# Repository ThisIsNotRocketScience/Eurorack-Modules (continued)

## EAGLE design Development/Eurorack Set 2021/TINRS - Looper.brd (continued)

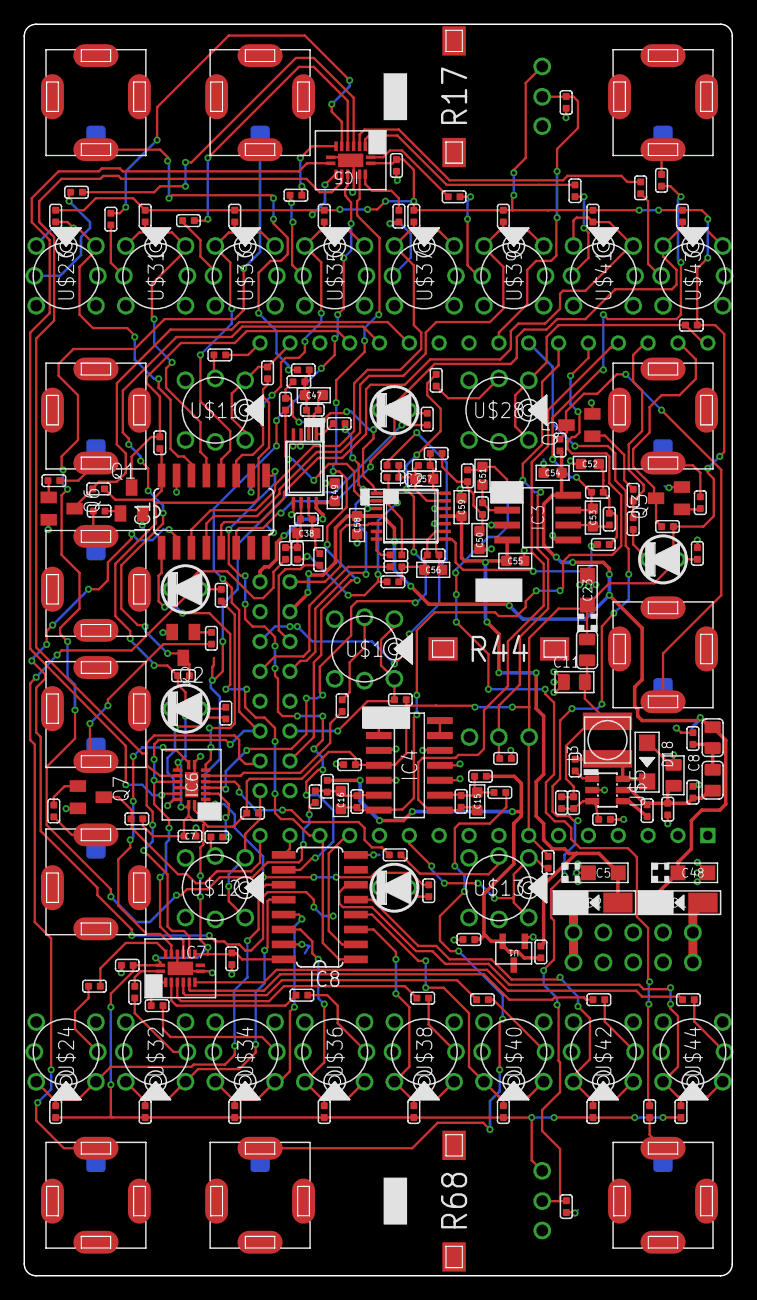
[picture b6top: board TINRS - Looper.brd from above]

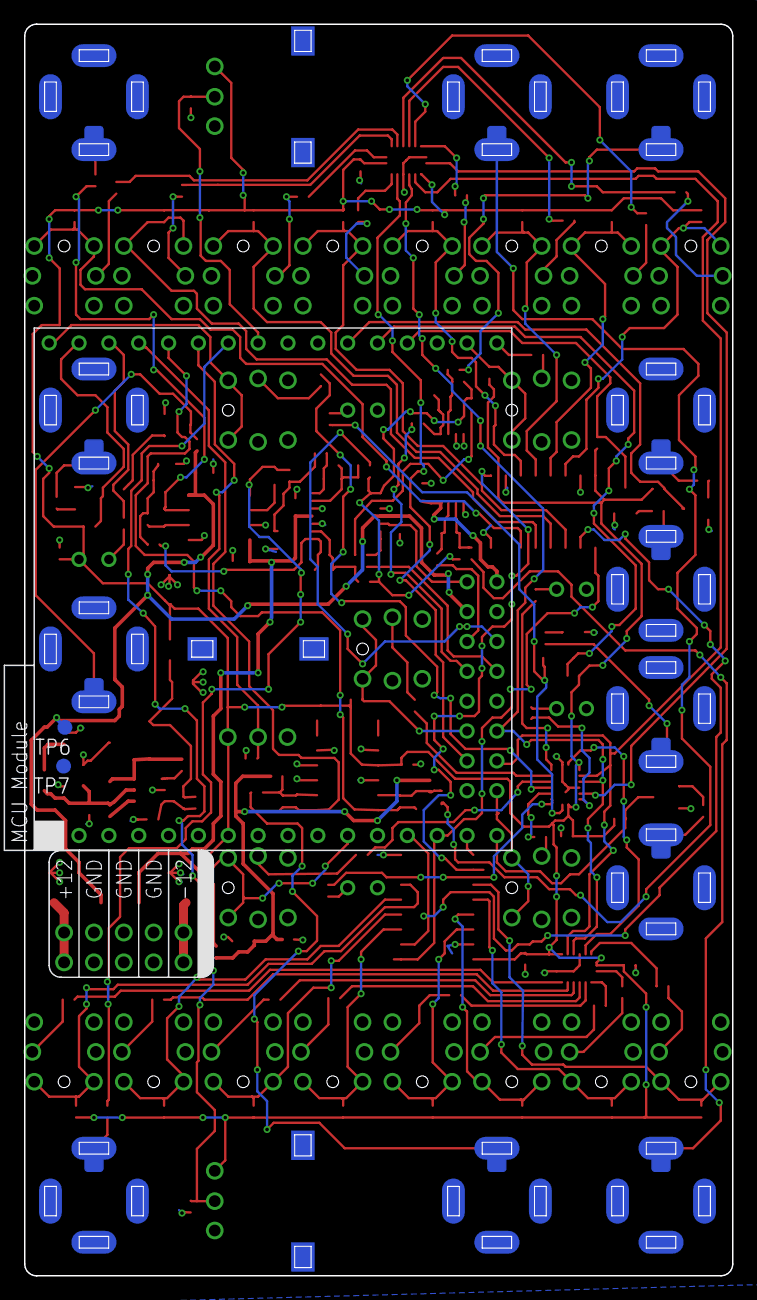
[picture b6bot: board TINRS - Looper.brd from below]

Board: 2 copper layers, 60.2 x 106.5 mm, 198 parts (4 on the bottom side), 151 nets.

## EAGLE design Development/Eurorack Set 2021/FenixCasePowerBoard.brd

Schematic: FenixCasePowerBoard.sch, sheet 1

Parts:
U$1, U$2, U$29, U$30: VOLTAGETESTPAD; POWERTESTPAD
U$4, U$6, U$7, U$12, U$104, U$105: VOLTAGETESTPAD_BIG; POWERTESTPAD_BIG
U$8: BACKPLANECONNECTOR_VINPLANE; BACKPLANECONNECTOR
U$20, U$21: TINRS_ARTWORKTINYDATE; JUSTATINYROCKET_DATECODE

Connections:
5V: U$7.P$1, U$7.P$2, U$7.P$3, U$8.22 (5V); also elsewhere on the board
12V: U$8.11 (12V), U$12.P$1, U$12.P$2, U$12.P$3; also elsewhere on the board
-12V: U$4.P$1, U$4.P$2, U$4.P$3, U$8.13 (-12V); also elsewhere on the board
AUDIO_OUT_LEFT_TIP: U$8.18 (AUDIO_OUT_LEFT), U$29.P$1, U$29.P$2, U$29.P$3
AUDIO_OUT_RIGHT_TIP: U$8.16 (AUDIO_OUT_RIGHT), U$30.P$1, U$30.P$2, U$30.P$3
GND: U$6.P$1, U$6.P$2, U$6.P$3, U$8.2 (GND), U$8.4 (GND), U$8.6 (GND), U$8.8 (GND), U$8.10 (GND), U$8.12 (GND), U$8.14 (GND), U$8.15 (GND), U$8.17 (GND), U$8.19 (GND), U$8.21 (GND), U$8.23 (GND), U$105.P$1, U$105.P$2, U$105.P$3; also elsewhere on the board
unnamed: U$1.P$1, U$1.P$2, U$1.P$3, U$8.24 (MIDI)
unnamed: U$2.P$1, U$2.P$2, U$2.P$3, U$8.20 (AUDIO_IN)
VIN: U$8.1 (VIN), U$8.3 (VIN), U$8.5 (VIN), U$8.7 (VIN), U$8.9 (VIN), U$104.P$1, U$104.P$2, U$104.P$3; also elsewhere on the board

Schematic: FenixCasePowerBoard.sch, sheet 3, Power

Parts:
H7, H8, H9, H10, H11, H12: MOUNT-HOLE3.6; 3,6
J1, J2, J3, J4, J5, J6, J7, J8, J9, J10, J11, J12, J13, J14, J15, J16, J17, J18, J19, J20, J21, J22, J23, J24, J25, J26: POWERSHROUDED; POWER_16_SHROUDED
U$5: FENIXPOWERBACKPACKART_MODULE; FENIXPOWERBACKPACK_MODULE
U$10: HEARTOFGOLD
U$31: FENIXPOWERBACKPACK_MODULE; FENIXPOWERBACKPACK

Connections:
5V: J1.11 (+5V), J1.12 (+5V), J2.11 (+5V), J2.12 (+5V), J3.11 (+5V), J3.12 (+5V), J4.11 (+5V), J4.12 (+5V), J5.11 (+5V), J5.12 (+5V), J6.11 (+5V), J6.12 (+5V), J7.11 (+5V), J7.12 (+5V), J8.11 (+5V), J8.12 (+5V), J9.11 (+5V), J9.12 (+5V), J10.11 (+5V), J10.12 (+5V), J11.11 (+5V), J11.12 (+5V), J12.11 (+5V), J12.12 (+5V), J13.11 (+5V), J13.12 (+5V), J14.11 (+5V), J14.12 (+5V), J15.11 (+5V), J15.12 (+5V), J16.11 (+5V), J16.12 (+5V), J17.11 (+5V), J17.12 (+5V), J18.11 (+5V), J18.12 (+5V), J19.11 (+5V), J19.12 (+5V), J20.11 (+5V), J20.12 (+5V), J21.11 (+5V), J21.12 (+5V), J22.11 (+5V), J22.12 (+5V), J23.11 (+5V), J23.12 (+5V), J24.11 (+5V), J24.12 (+5V), J25.11 (+5V), J25.12 (+5V), J26.11 (+5V), J26.12 (+5V), U$31.5V@1 (5V), U$31.5V@2 (5V), U$31.5V@3 (5V), U$31.5V@4 (5V); also elsewhere on the board
10V: U$31.10V, U$31.10V@2 (10V)
12V: J1.9 (+12V), J1.10 (+12V), J2.9 (+12V), J2.10 (+12V), J3.9 (+12V), J3.10 (+12V), J4.9 (+12V), J4.10 (+12V), J5.9 (+12V), J5.10 (+12V), J6.9 (+12V), J6.10 (+12V), J7.9 (+12V), J7.10 (+12V), J8.9 (+12V), J8.10 (+12V), J9.9 (+12V), J9.10 (+12V), J10.9 (+12V), J10.10 (+12V), J11.9 (+12V), J11.10 (+12V), J12.9 (+12V), J12.10 (+12V), J13.9 (+12V), J13.10 (+12V), J14.9 (+12V), J14.10 (+12V), J15.9 (+12V), J15.10 (+12V), J16.9 (+12V), J16.10 (+12V), J17.9 (+12V), J17.10 (+12V), J18.9 (+12V), J18.10 (+12V), J19.9 (+12V), J19.10 (+12V), J20.9 (+12V), J20.10 (+12V), J21.9 (+12V), J21.10 (+12V), J22.9 (+12V), J22.10 (+12V), J23.9 (+12V), J23.10 (+12V), J24.9 (+12V), J24.10 (+12V), J25.9 (+12V), J25.10 (+12V), J26.9 (+12V), J26.10 (+12V), U$31.12V@1 (12V), U$31.12V@2 (12V), U$31.12V@4 (12V); also elsewhere on the board
-5V: U$31.-5V, U$31.-5V@2 (-5V)
-12V: J1.1 (-12V), J1.2 (-12V), J2.1 (-12V), J2.2 (-12V), J3.1 (-12V), J3.2 (-12V), J4.1 (-12V), J4.2 (-12V), J5.1 (-12V), J5.2 (-12V), J6.1 (-12V), J6.2 (-12V), J7.1 (-12V), J7.2 (-12V), J8.1 (-12V), J8.2 (-12V), J9.1 (-12V), J9.2 (-12V), J10.1 (-12V), J10.2 (-12V), J11.1 (-12V), J11.2 (-12V), J12.1 (-12V), J12.2 (-12V), J13.1 (-12V), J13.2 (-12V), J14.1 (-12V), J14.2 (-12V), J15.1 (-12V), J15.2 (-12V), J16.1 (-12V), J16.2 (-12V), J17.1 (-12V), J17.2 (-12V), J18.1 (-12V), J18.2 (-12V), J19.1 (-12V), J19.2 (-12V), J20.1 (-12V), J20.2 (-12V), J21.1 (-12V), J21.2 (-12V), J22.1 (-12V), J22.2 (-12V), J23.1 (-12V), J23.2 (-12V), J24.1 (-12V), J24.2 (-12V), J25.1 (-12V), J25.2 (-12V), J26.1 (-12V), J26.2 (-12V), U$31.-12V@1 (-12V), U$31.-12V@2 (-12V), U$31.-12V@3 (-12V); also elsewhere on the board
CV: J1.13 (CV), J1.14 (CV), J2.13 (CV), J2.14 (CV), J3.13 (CV), J3.14 (CV), J4.13 (CV), J4.14 (CV), J5.13 (CV), J5.14 (CV), J6.13 (CV), J6.14 (CV), J7.13 (CV), J7.14 (CV), J8.13 (CV), J8.14 (CV), J9.13 (CV), J9.14 (CV), J10.13 (CV), J10.14 (CV), J11.13 (CV), J11.14 (CV), J12.13 (CV), J12.14 (CV), J13.13 (CV), J13.14 (CV), J14.13 (CV), J14.14 (CV), J15.13 (CV), J15.14 (CV), J16.13 (CV), J16.14 (CV), J17.13 (CV), J17.14 (CV), J18.13 (CV), J18.14 (CV), J19.13 (CV), J19.14 (CV), J20.13 (CV), J20.14 (CV), J21.13 (CV), J21.14 (CV), J22.13 (CV), J22.14 (CV), J23.13 (CV), J23.14 (CV), J24.13 (CV), J24.14 (CV), J25.13 (CV), J25.14 (CV), J26.13 (CV), J26.14 (CV)
GATE: J1.15 (GATE), J1.16 (GATE), J2.15 (GATE), J2.16 (GATE), J3.15 (GATE), J3.16 (GATE), J4.15 (GATE), J4.16 (GATE), J5.15 (GATE), J5.16 (GATE), J6.15 (GATE), J6.16 (GATE), J7.15 (GATE), J7.16 (GATE), J8.15 (GATE), J8.16 (GATE), J9.15 (GATE), J9.16 (GATE), J10.15 (GATE), J10.16 (GATE), J11.15 (GATE), J11.16 (GATE), J12.15 (GATE), J12.16 (GATE), J13.15 (GATE), J13.16 (GATE), J14.15 (GATE), J14.16 (GATE), J15.15 (GATE), J15.16 (GATE), J16.15 (GATE), J16.16 (GATE), J17.15 (GATE), J17.16 (GATE), J18.15 (GATE), J18.16 (GATE), J19.15 (GATE), J19.16 (GATE), J20.15 (GATE), J20.16 (GATE), J21.15 (GATE), J21.16 (GATE), J22.15 (GATE), J22.16 (GATE), J23.15 (GATE), J23.16 (GATE), J24.15 (GATE), J24.16 (GATE), J25.15 (GATE), J25.16 (GATE), J26.15 (GATE), J26.16 (GATE)
GND: J1.3 (GND), J1.4 (GND), J1.5 (GND), J1.6 (GND), J1.7 (GND), J1.8 (GND), J2.3 (GND), J2.4 (GND), J2.5 (GND), J2.6 (GND), J2.7 (GND), J2.8 (GND), J3.3 (GND), J3.4 (GND), J3.5 (GND), J3.6 (GND), J3.7 (GND), J3.8 (GND), J4.3 (GND), J4.4 (GND), J4.5 (GND), J4.6 (GND), J4.7 (GND), J4.8 (GND), J5.3 (GND), J5.4 (GND), J5.5 (GND), J5.6 (GND), J5.7 (GND), J5.8 (GND), J6.3 (GND), J6.4 (GND), J6.5 (GND), J6.6 (GND), J6.7 (GND), J6.8 (GND), J7.3 (GND), J7.4 (GND), J7.5 (GND), J7.6 (GND), J7.7 (GND), J7.8 (GND), J8.3 (GND), J8.4 (GND), J8.5 (GND), J8.6 (GND), J8.7 (GND), J8.8 (GND), J9.3 (GND), J9.4 (GND), J9.5 (GND), J9.6 (GND), J9.7 (GND), J9.8 (GND), J10.3 (GND), J10.4 (GND), J10.5 (GND), J10.6 (GND), J10.7 (GND), J10.8 (GND), J11.3 (GND), J11.4 (GND), J11.5 (GND), J11.6 (GND), J11.7 (GND), J11.8 (GND), J12.3 (GND), J12.4 (GND), J12.5 (GND), J12.6 (GND), J12.7 (GND), J12.8 (GND), J13.3 (GND), J13.4 (GND), J13.5 (GND), J13.6 (GND), J13.7 (GND), J13.8 (GND), J14.3 (GND), J14.4 (GND), J14.5 (GND), J14.6 (GND), J14.7 (GND), J14.8 (GND), J15.3 (GND), J15.4 (GND), J15.5 (GND), J15.6 (GND), J15.7 (GND), J15.8 (GND), J16.3 (GND), J16.4 (GND), J16.5 (GND), J16.6 (GND), J16.7 (GND), J16.8 (GND), J17.3 (GND), J17.4 (GND), J17.5 (GND), J17.6 (GND), J17.7 (GND), J17.8 (GND), J18.3 (GND), J18.4 (GND), J18.5 (GND), J18.6 (GND), J18.7 (GND), J18.8 (GND), J19.3 (GND), J19.4 (GND), J19.5 (GND), J19.6 (GND), J19.7 (GND), J19.8 (GND), J20.3 (GND), J20.4 (GND), J20.5 (GND), J20.6 (GND), J20.7 (GND), J20.8 (GND), J21.3 (GND), J21.4 (GND), J21.5 (GND), J21.6 (GND), J21.7 (GND), J21.8 (GND), J22.3 (GND), J22.4 (GND), J22.5 (GND), J22.6 (GND), J22.7 (GND), J22.8 (GND), J23.3 (GND), J23.4 (GND), J23.5 (GND), J23.6 (GND), J23.7 (GND), J23.8 (GND), J24.3 (GND), J24.4 (GND), J24.5 (GND), J24.6 (GND), J24.7 (GND), J24.8 (GND), J25.3 (GND), J25.4 (GND), J25.5 (GND), J25.6 (GND), J25.7 (GND), J25.8 (GND), J26.3 (GND), J26.4 (GND), J26.5 (GND), J26.6 (GND), J26.7 (GND), J26.8 (GND), U$31.GND@1 (GND), U$31.GND@2 (GND), U$31.GND@3 (GND), U$31.GND@4 (GND), U$31.GND@5 (GND), U$31.GND@6 (GND), U$31.GND@7 (GND), U$31.GND@8 (GND), U$31.GND@9 (GND), U$31.GND@10 (GND), U$31.GND@11 (GND), U$31.GND@12 (GND), U$31.GND@13 (GND), U$31.GND@14 (GND); also elsewhere on the board
VIN: U$31.VIN@1 (VIN(18V)), U$31.VIN@2 (VIN(18V)), U$31.VIN@3 (VIN(18V)), U$31.VIN@4 (VIN(18V)); also elsewhere on the board

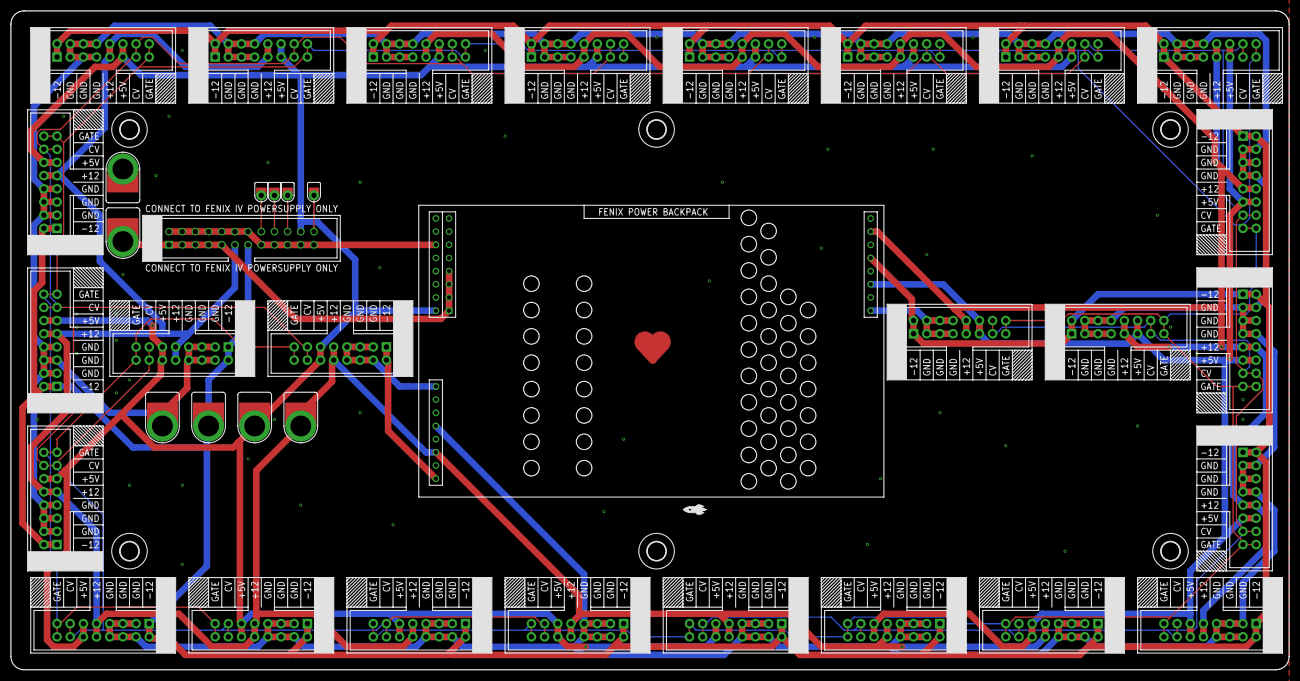
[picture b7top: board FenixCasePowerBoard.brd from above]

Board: 2 copper layers, 246.4 x 127.0 mm, 48 parts (1 on the bottom side), 13 nets.

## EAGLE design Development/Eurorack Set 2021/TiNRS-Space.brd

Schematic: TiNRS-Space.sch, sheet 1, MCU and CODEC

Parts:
C1, C2: 2.2n; C0603
C27, C34, C40, C44, C45: 10u; CASE-A_3216
C28, C31, C41: 100n; C0402
C42, C43: 100n; C0603
IC1: PCM3060; TSSOP-28
NODRILL_TESTPAD2, NODRILL_TESTPAD3, NODRILL_TESTPAD4, NODRILL_TESTPAD5, NODRILL_TESTPAD6, NODRILL_TESTPAD7, NODRILL_TESTPAD8, NODRILL_TESTPAD9: AUDIO-JACK_SMALLSYMBOL; 3.5MM-JACK-SWITCH-13MM-NOHOLES-TESTPAD
Q1: MMBT3904; SOT23-BEC; MPN PMBT3904,215
R13: 100k; R0603
R14: 10k; R0603
R38: 56; R0603
TP1, TP3, TP4, TP5: TPB2,54; B2,54
U2: CJ1117-5.0; SOT223
U$3: PINHD-1X10; 1X10-BIG
U$5: TEENSY_4.0
U$9, U$27, U$28, U$31: SWITCH_W_LED_PB6149L-X-102YELLOW; PB6149L

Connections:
3.3V: C40.+ (1), C41.1, IC1.7 (VDD), R14.2, U$3.7; also elsewhere on the board
5V: C31.2, C34.+ (1), C43.1, C44.+ (1), IC1.24 (VCC), U2.2 (OUT), U2.TER (OUT), U$5.VIN
12V: C42.1, C45.+ (1), U2.3 (IN), U$3.6; also elsewhere on the board
ADC0: U$5.14/A0 (14/A0/TX3); also elsewhere on the board
ADC1: U$5.15/A1 (15/A1/RX3); also elsewhere on the board
ADC2: U$5.16/A2 (16/A2/RX4); also elsewhere on the board
ADC3: U$5.17/A3 (17/A3/TX4); also elsewhere on the board
ADC4: U$5.18/A4/SDA; also elsewhere on the board
ADC5: U$5.19/A5/SCL; also elsewhere on the board
BIAS_AUDIO: C27.+ (1), C28.1, IC1.21 (VCOM), U$3.3
CLOCK: U$5.2; also elsewhere on the board
CODEC_SCL: IC1.1 (MC/SCL/FMT), U$5.0/RX (0/RX1)
CODEC_SDA: IC1.2 (MD/SDA/DEMP), U$5.1/TX (1/TX1)
FREEZEBUTTON: U$5.11/MOSI, U$9.1, U$9.2
FREEZEBUTTONLED: R38.2; also elsewhere on the board
FREEZEJACK: Q1.C, R14.1, U$5.12/MISO
GND: C1.2, C2.2, C27.- (2), C28.2, C31.1, C34.- (2), C40.- (2), C41.2, C42.2, C43.2, C44.- (2), C45.- (2), IC1.8 (DGND), IC1.9 (SCKI2), IC1.10 (BCK2), IC1.11 (LRCK2), IC1.16 (SGND), IC1.22 (AGND2), IC1.23 (AGND1), IC1.27 (!MS!/ADR/IFMD), IC1.28 (MODE), NODRILL_TESTPAD9.RING_B@1 (RING), NODRILL_TESTPAD9.RING_T@3 (RING), NODRILL_TESTPAD9.SWITCH_B@1 (SWITCH), NODRILL_TESTPAD9.SWITCH_T@3 (SWITCH), Q1.E, U2.1 (GND), U$3.8, U$5.GND, U$5.GND2, U$5.GND3, U$9.3, U$9.4, U$9.LEDNEG (NEG); also elsewhere on the board
I2S_BCK1: IC1.5 (BCK1), U$5.21/A7 (21/A7/RX5)
I2S_DIN: IC1.12 (DIN), U$5.7 (7/RX2)
I2S_DOUT: IC1.3 (DOUT), U$5.8 (8/TX2)
I2S_LRCK1: IC1.4 (LRCK1), U$5.20/A6 (20/A6/TX5)
I2S_SCKI1: IC1.6 (SCKI1), U$5.23/A9
INL: C2.1, IC1.25 (VINL), U$3.2
INR: C1.1, IC1.26 (VINR), U$3.1
LATCH: U$5.3/CANTX (3); also elsewhere on the board
unnamed: IC1.20 (VOUTL+), U$3.4
unnamed: IC1.18 (VOUTR+), U$3.5
unnamed: IC1.19 (VOUTL-), TP1.TP
unnamed: IC1.15 (!RST!), U$3.10
unnamed: IC1.17 (VOUTR-), TP3.TP
unnamed: IC1.13 (ZEROR), TP4.TP
unnamed: IC1.14 (ZEROL), TP5.TP
unnamed: Q1.B, R13.2
unnamed: NODRILL_TESTPAD9.TIP_B@1 (TIP), NODRILL_TESTPAD9.TIP_T@3 (TIP), R13.1
unnamed: R38.1, U$9.LEDPOS (POS)
SHIFTERS: U$5.4/CANRX (4); also elsewhere on the board

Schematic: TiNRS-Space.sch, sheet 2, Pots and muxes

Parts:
C3, C4, C9, C10, C15, C16, C30, C37, C47, C52, C53, C67, C68, C69, C70, C71, C72, C73, C74: 100n; C0402
IC2, IC4, IC9: 4052D; SO16
R1, R4, R5, R6, R7, R10, R11, R12, R17, R18, R19, R20, R23, R46, R47, R48: 10kB; ALPS_POT_SQUAREHOLES

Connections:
3.3V: C15.2, C16.2, C74.2, IC2.16 (VCC), IC4.16 (VCC), IC9.16 (VCC), R1.P$3 (A), R4.P$3 (A), R5.P$3 (A), R6.P$3 (A), R7.P$3 (A), R10.P$3 (A), R11.P$3 (A), R12.P$3 (A), R17.P$3 (A), R18.P$3 (A), R19.P$3 (A), R20.P$3 (A), R23.P$3 (A), R46.P$3 (A), R47.P$3 (A), R48.P$3 (A); also elsewhere on the board
A1: C9.2, IC4.12 (X0), R11.P$2 (S)
A2: C70.2, IC4.14 (X1), R5.P$2 (S)
A3: C69.2, IC4.15 (X2), R4.P$2 (S)
A4: C47.2, IC4.11 (X3), R23.P$2 (S)
A5: C3.2, IC4.1 (Y0), R1.P$2 (S)
A6: C37.2, IC4.5 (Y1), R46.P$2 (S)
A7: C30.2, IC4.2 (Y2), R48.P$2 (S)
A8: C10.2, IC4.4 (Y3), R12.P$2 (S)
ADC0: IC2.13 (X); also elsewhere on the board
ADC1: IC2.3 (Y); also elsewhere on the board
ADC2: IC4.13 (X); also elsewhere on the board
ADC3: IC4.3 (Y); also elsewhere on the board
ADC4: IC9.13 (X); also elsewhere on the board
ADC5: IC9.3 (Y); also elsewhere on the board
B1: C72.2, IC2.12 (X0), R7.P$2 (S)
B2: C71.2, IC2.14 (X1), R47.P$2 (S)
B3: C68.2, IC2.15 (X2), R17.P$2 (S)
B4: C67.2, IC2.11 (X3), R18.P$2 (S)
B5: C53.2, IC2.1 (Y0), R20.P$2 (S)
B6: C52.2, IC2.5 (Y1), R19.P$2 (S)
B7: C73.2, IC2.2 (Y2), R6.P$2 (S)
B8: C4.2, IC2.4 (Y3), R10.P$2 (S)
C1: IC9.12 (X0)
C2: IC9.14 (X1)
C3: IC9.15 (X2)
C4: IC9.11 (X3)
C5: IC9.1 (Y0)
C6: IC9.5 (Y1)
C7: IC9.2 (Y2)
C8: IC9.4 (Y3)
GND: C3.1, C4.1, C9.1, C10.1, C15.1, C16.1, C30.1, C37.1, C47.1, C52.1, C53.1, C67.1, C68.1, C69.1, C70.1, C71.1, C72.1, C73.1, C74.1, IC2.6 (INH), IC2.7 (VEE), IC2.8 (GND), IC4.6 (INH), IC4.7 (VEE), IC4.8 (GND), IC9.6 (INH), IC9.7 (VEE), IC9.8 (GND), R1.P$1 (E), R4.P$1 (E), R5.P$1 (E), R6.P$1 (E), R7.P$1 (E), R10.P$1 (E), R11.P$1 (E), R12.P$1 (E), R17.P$1 (E), R18.P$1 (E), R19.P$1 (E), R20.P$1 (E), R23.P$1 (E), R46.P$1 (E), R47.P$1 (E), R48.P$1 (E); also elsewhere on the board
MUX_A: IC2.10 (A), IC4.10 (A), IC9.10 (A)
MUX_B: IC2.9 (B), IC4.9 (B), IC9.9 (B)

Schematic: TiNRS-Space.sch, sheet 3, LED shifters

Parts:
C7, C14, C20, C22: 100nF; C0603; MPN MC0603F104Z160CT
D4, D5, D6, D7, D8, D9, D10, D11, D12, D13, D14, D24, D25, D26, D27, D28, D29, D30, D31, D32, D33, D34, D35: yellow; 3MMLED
IC5, IC6, IC7, IC8: 74HC595BQ; QFN50P250X350X100-17N
R2, R3, R8, R9, R31, R32, R33, R34, R49, R54, R55, R56, R58, R59, R60, R61, R62, R63, R64, R65, R66, R70, R71: 56; R0603

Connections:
3.3V: C7.2, C14.2, C20.2, C22.2, IC5.10 (!MR), IC5.16 (VCC), IC6.10 (!MR), IC6.16 (VCC), IC7.10 (!MR), IC7.16 (VCC), IC8.10 (!MR), IC8.16 (VCC); also elsewhere on the board
CLOCK: IC5.11 (SHCP), IC6.11 (SHCP), IC7.11 (SHCP), IC8.11 (SHCP); also elsewhere on the board
FREEZEBUTTONLED: IC6.6 (Q6); also elsewhere on the board
GND: C7.1, C14.1, C20.1, C22.1, D4.-, D5.-, D6.-, D7.-, D8.-, D9.-, D10.-, D11.-, D12.-, D13.-, D14.-, D24.-, D25.-, D26.-, D27.-, D28.-, D29.-, D30.-, D31.-, D32.-, D33.-, D34.-, D35.-, IC5.8 (GND), IC5.13 (!OE), IC5.17 (GND_2), IC6.8 (GND), IC6.13 (!OE), IC6.17 (GND_2), IC7.8 (GND), IC7.13 (!OE), IC7.17 (GND_2), IC8.8 (GND), IC8.13 (!OE), IC8.17 (GND_2); also elsewhere on the board
LATCH: IC5.12 (STCP), IC6.12 (STCP), IC7.12 (STCP), IC8.12 (STCP); also elsewhere on the board
unnamed: IC5.15 (Q0), R33.2
unnamed: D7.+, R8.1
unnamed: IC5.1 (Q1), R64.2
unnamed: IC5.2 (Q2), R63.2
unnamed: IC5.3 (Q3), R61.2
unnamed: D28.+, R62.1
unnamed: IC5.4 (Q4), R62.2
unnamed: IC5.5 (Q5), R2.2
unnamed: D29.+, R61.1
unnamed: IC5.6 (Q6), R56.2
unnamed: IC5.7 (Q7), R58.2
unnamed: IC6.3 (Q3), R59.2
unnamed: IC7.7 (Q7), R54.2
unnamed: IC7.6 (Q6), R55.2
unnamed: IC7.5 (Q5), R8.2
unnamed: D13.+, R70.1
unnamed: IC7.4 (Q4), R3.2
unnamed: D6.+, R3.1
unnamed: D5.+, R9.1
unnamed: D4.+, R49.1
unnamed: D8.+, R55.1
unnamed: D9.+, R54.1
unnamed: D10.+, R60.1
unnamed: D11.+, R65.1
unnamed: IC7.3 (Q3), R9.2
unnamed: IC7.2 (Q2), R49.2
unnamed: IC7.1 (Q1), R32.2
unnamed: IC7.15 (Q0), R65.2
unnamed: IC6.7 (Q7), R60.2
unnamed: D14.+, R71.1
unnamed: IC8.1 (Q1), R71.2
unnamed: IC8.2 (Q2), R70.2
unnamed: D12.+, R66.1
unnamed: IC8.3 (Q3), R31.2
unnamed: IC8.4 (Q4), R34.2
unnamed: IC8.5 (Q5), R66.2
unnamed: D27.+, R2.1
unnamed: D26.+, R56.1
unnamed: D25.+, R58.1
unnamed: D24.+, R59.1
unnamed: D30.+, R63.1
unnamed: D31.+, R64.1
unnamed: D32.+, R33.1
unnamed: D33.+, R32.1
unnamed: D34.+, R31.1
unnamed: D35.+, R34.1
OUT_LFOCYCLEMID: IC6.5 (Q5)
OUT_LFOCYCLESTART: IC6.4 (Q4)
SHIFTER1TO2: IC5.9 (Q7S), IC6.14 (DS)
SHIFTERS: IC5.14 (DS); also elsewhere on the board
SHIFTERS2TO3: IC6.9 (Q7S), IC7.14 (DS)
SHIFTERS3TO4: IC7.9 (Q7S), IC8.14 (DS)

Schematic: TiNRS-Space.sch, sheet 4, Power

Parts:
C5, C12, C13, C17, C23, C33: 10uF; CASE-A_3216; MPN TAJB106K020RNJ
C6: 100nF; C0603; MPN 06035C104KAT2A
C8, C11, C19, C24, C25: 100nF; C0603; MPN MC0603F104Z160CT
C18: 10n; C0603; MPN MC0603F104Z160CT
C26: 33p; C0603; MPN MC0603F104Z160CT
C32: 22u; CASE-A_3216; MPN TAJB106K020RNJ
D1, D2: MRA4004T3G; DO-214AC; MPN US1G-E3/5AT
D3: D-SMA; DO-214AC
IC3: LD1117AS33TR; SOT223; MPN LD1117AS33TR
J14: POWERSHROUDED; POWER_16_SHROUDED
L1, L2, L4: 0.1uH; L0805
L3: 4.7uH; L0420
R15: 100k; R0603
R16: 120k; R0603
R21: 22k; R0603
R26: 10k; R0603
U1: LM4040DIM3-5.0; SOT95P237X112-3N
U$29: BL9342; SOT23-6

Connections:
3.3V: C8.2, C12.+ (1), C23.+ (1), IC3.2 (OUT), IC3.4 (OUT); also elsewhere on the board
5V_NEWREG: L4.2
12V: C11.2, C13.+ (1), C33.+ (1), D1.2 (-), IC3.3 (IN), L1.1; also elsewhere on the board
-12V: C5.- (2), D2.1 (+), R26.1
GND: C5.+ (1), C6.1, C8.1, C11.1, C12.- (2), C13.- (2), C17.- (2), C18.1, C19.1, C23.- (2), C24.1, C32.- (2), C33.- (2), D3.1 (+), IC3.1 (ADJ), J14.3 (GND), J14.4 (GND), J14.5 (GND), J14.6 (GND), J14.7 (GND), J14.8 (GND), R21.2, U1.1 (CATHODE), U$29.2 (GND); also elsewhere on the board
unnamed: C18.2, L1.2, L2.1
unnamed: C17.+ (1), C19.2, C24.2, L2.2, R15.2, U$29.5 (VIN)
unnamed: R15.1, U$29.4 (EN)
unnamed: C25.2, U$29.1 (BST)
unnamed: D1.1 (+), J14.9 (+12V), J14.10 (+12V)
unnamed: C25.1, D3.2 (-), L3.1, U$29.6 (SW)
unnamed: C26.2, R16.2, R21.1, U$29.3 (FB)
unnamed: C26.1, C32.+ (1), L3.2, L4.1, R16.1
unnamed: D2.2 (-), J14.1 (-12V), J14.2 (-12V)
REF_-5V: C6.2, R26.2, U1.2 (ANODE)

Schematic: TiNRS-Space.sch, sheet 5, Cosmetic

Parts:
PCB1: EURORACK_PCB24HP; EURORACK24HPPCB
U$4: TINRS_ARTWORKLOGO; TINRSLOGO

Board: 2 copper layers, 160 parts (3 on the bottom side), 114 nets, no tracks yet.

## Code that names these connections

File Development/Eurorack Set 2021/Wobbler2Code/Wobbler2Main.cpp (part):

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#define DAC_CS 1
#define DAC_DAT 2

#define FASTMODE_BUT 5

#define SR_2_DAT 9
#define SR_2_CLK 10
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#define SR_1_CLK 13
#define SR_1_LATCH 14

#define RESET_PATTERN_BUT 20
#define RESET_PATTERN 21
#define SYNC_LFO 22
#define MUX_A 24
#define MUX_B 25

#define ADC_MUX0 ADC0
#define ADC_MUX1 ADC1
#define ADC_FREQ ADC2
#define ADC_SHAPE ADC3

uint16_t COMBINE(int32_t A, int32_t B)
{
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    return (uint16_t)R;
}

#define KNOB_MOD muxed[0][0]
#define KNOB_FREQ muxed[0][1]
#define KNOB_SHAPE muxed[0][2]
#define KNOB_PHASE muxed[0][3]

#define ADC_PHASE muxed[1][0]
#define ADC_MOD muxed[1][1]
#define KNOB_PHASED muxed[1][2]
#define KNOB_NORMAL muxed[1][3]
#include "Wobbler2.h"
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        gpio_put(clk, 1);
        gpio_put(clk, 0);
    }
    gpio_put(latch, 1);
    gpio_put(latch, 0);
}

uint8_t pwm = 0;
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    Wobbler2_Init(&TheWobbler);
    int curmux = 0;

    gpio_init(RESET_PATTERN_BUT);
    gpio_dir(RESET_PATTERN_BUT, GPIO_IN);
    gpio_pull_up(RESET_PATTERN_BUT);

    gpio_init(RESET_PATTERN);
    gpio_dir(RESET_PATTERN, GPIO_IN);
    gpio_pull_up(RESET_PATTERN);

    gpio_init(FASTMODE_BUT);
    gpio_dir(FASTMODE_BUT, GPIO_IN);
    gpio_pull_up(FASTMODE_BUT);
    gpio_init(MUX_A);
    gpio_dir(MUX_A, GPIO_OUT);
    gpio_init(MUX_B);
    gpio_dir(MUX_B, GPIO_OUT);

    gpio_init(DAC_CS);
    gpio_dir(DAC_CS, GPIO_OUT);
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
        curmux = (curmux + 1) % 4;
        if ((curmux & 1) == 1)
            gpio_put(MUX_A, 1);
        else
            gpio_put(MUX_A, 0);
        if ((curmux & 2) == 2)
            gpio_put(MUX_B, 1);
        else
            gpio_put(MUX_B, 0);
        adc_input_select(0);
        muxed[0][curmux] = adc_read() * 16;
        adc_input_select(1);
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// but we are using a threshold of 8 here (consume 1 byte from each FIFO entry
// and discard the remainder) to make things easier for software on the other side

static inline void spi_on_pio_init(PIO pio, uint sm, uint offset, uint data_pin, uint clk_pin, float clk_div) {
    pio_gpio_init(pio, data_pin);
    pio_gpio_init(pio, clk_pin);
    pio_sm_set_consecutive_pindirs(pio, sm, data_pin, 1, true);
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
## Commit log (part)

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2015-10-31 Initial commit - boards in a terrible state so far
    Tadaaa
2015-10-31 Parts libs for euroracks
2015-10-31 Power on the multiples board
2015-11-01 K22 baseboard part outline
2015-11-01 Updated input/output jacks
2015-11-03 Goldfish Frontpanel Progress + eurolib extensions
2015-11-04 ScaleOffset board nearing readiness
2015-11-04 Updated europarts library in all boards.
2015-11-05 Redone most of the goldfish front cv summing, added opamps to library
2015-11-05 Fixed up scaleoffset module. Added cv and gate outputs
2015-11-05 GateRhythm added
2015-11-05 GateRhythm cleanup + decoupling + routing.
2015-11-05 LogicThingie - extra button, no serial, better routing
2015-11-05 Routing updates and ScaleOffset to 6hp
2015-11-05 Cleaning up folder
2015-11-05 Goldfish update by Lauri - ScaleOffset fix
2015-11-05 Lots of board updates
2015-11-05 Fix K22 baseboard pinout
2015-11-06 Buffered Multipes Spacepacked
2015-11-06 TestBench - initial commit
2015-11-06 Added inverted silk for 10pin power - added opamps for leds
2015-11-06 DRC & ERC on all boards = green now.
2015-11-06 Added holes to the panel layer to create complete lasercutter dxf exports possible
2015-11-09 Renamed LogicThingie to SonicScrewdriver - cosmetic changes, panel exports, cam folders
2015-11-09 Opamp Devboard added
2015-11-11 Added LauriFilter MCUfront - updated opamp board with formulas
2015-11-11 TimeLord board + minor gaterhythm update
2015-11-11 LauriFilter has switches + 595 for leds
2015-11-11 Many many changes after crosschecking by Lauri
2015-11-13 TimeLord update
2015-11-17 pre order fixes
2015-11-17 Pre-order fixes
2015-11-19 eurorack prototyping board added
2015-11-19 updated protoboard with better attiny area
2015-11-19 repo cleanup
2015-11-19 frontpanel designs
2015-11-19 more repo cleaning + Readme
2015-11-19 DipTrace files for the codec and power supply.
2015-11-23 small cosmetic changes- reversed the led polarity
2015-12-02 BodgeFix 1 : multiples leds swapped + noted the inversion
2015-12-02 Bodge 2 - different led viz schematic for scaleoffset
2015-12-02 More bodges... different led setup for scaleoffset, gaterhythm still has buttons reversed
2015-12-03 GateRhythm updates - updated switch pattern in zephodlibrary (not in this repo)
2015-12-04 More bodgefixes + led reversals
2015-12-05 More bodges - -12v line on fishfront, leds reversal, protection resistors on sonicscrewdriver
2015-12-13 Codec pcb rev2.
2015-12-18 Shifted codecboard power connector by 50 mil.
2015-12-24 Changed drill radius for potentiometer in library
2016-01-18 Fiducials!
2016-01-19 Updated library shape for jacks - updated all boards to match
2016-01-27 Library updated for MCUBoard, many tweaks.
2016-01-30 LEDDistortion converted to board
2016-01-30 panel dxfs and LEDDistortion updates
2016-01-30 More lauri feedback incorporated
2016-01-30 Optional LR Phasor + serial switch jumper on LED distortion
2016-01-31 Full configurable LRC stage on the LEDDistortion - placement cleanup
2016-02-02 New busboard
2016-08-04 Finally some updates...
2016-08-25 ScrewDriver fixes - codecboard for series 2 added - passthrough board - melody initial
2016-08-26 Melody And Screwdriver Updates
2016-08-29 Melody progress
2016-08-30 Melody Updates
2016-09-01 Added Simple Switch Module - Added DESC attribute for some input elements
2016-09-05 added router settings, Melody polishing
2016-09-07 Clearance updates - removed double clocktrace
2016-09-10 4io frontpanel, trigger thinner
2016-09-15 Final tweaks for the order - initial bom update for tuesday
2016-09-29 eeprom pinout update
2016-09-30 Fixes to the BOM
2016-10-03 Tuesday r2 handrouted & panel details
2016-10-06 SMT-led version of the Tuesday Module
2016-10-10 Tuesday schematic updates for SMT led version, dxf for panel, gerber package
2016-10-18 Envelope Initital Commit
2016-10-24 Envelope Commit
2016-10-24 Wasp concept.. not sure about this
2016-11-07 Envelope Board and Schematic detail fixes
2016-11-10 Envelope Routing Progress
2016-11-10 Envelope Handrouting progress
2016-11-10 Envelope Board Routed
2016-11-10 More routing
2016-11-10 VCA board
2016-11-10 CodecThing and DelayFront
2016-11-10 Envelope Routing Optimizing
2016-11-11 VCA Rerouting
2016-11-11 Forgot to power one opamp.. whoops
2016-11-11 Cleanup
2016-11-12 VCA updates
2016-11-15 Frontpanel DXFs, VCA update, CVSummer fixes
2016-11-15 Summer and Envelope updates (leftover opamp wiring)
2016-11-24 Minor wasp tweaks.. nowhere near completion
2016-11-26 Many routing & artwork updates
2016-11-28 Some extra patterns
2016-11-30 Tiny routing updte
2016-12-02 Doublechecks & artwork prep
2016-12-03 Keychan and logos
2016-12-25 First Bodges for Envelope
2017-01-04 Tuesday bom fix (LD1117 wrong version)
2017-01-13 Assembly data fixes, VCA revision (lm13700 pinout reversal!), Wobbler revision (better opamp scaling)
2017-02-14 Quick Master Clock Board
2017-02-25 PowerBus + EnvFollower
2017-03-09 Jig, EnvFollower, Placement
2017-05-10 MANY new board tweaks since Superbooth!
2017-05-17 Create LICENSE
2017-05-31 EnvFollower values, bigfish fixes, wobbler updates, lineout clarifications
2017-06-20 LOTS of updates..... JUNE2017 prototype sprint!
2017-09-07 Progress..
2017-09-16 Wobbler Noise Upgrades & Adding extra shifter & LEDs
2017-09-17 Wobbler reroute complete - with opamp setup made smaller.
2017-09-17 Wobbler updates.
2017-09-17 More Libs :-)
2017-09-17 Wobbler and Edgecutter progress
2017-09-17 ld components
2017-09-18 Moved TuesdayR4 to new folder, updated library components to match latest insights.
2017-09-19 Many small routing fixes & tracewidth improvements. Also split the tuesday over multiple pages.
2017-09-20 FinalEffect & AddMixShift & EspDrum
2017-09-21 BigBus - Tuesday tracenames for calibration-fixups, Finaleffect/flask routed
2017-09-22 BusUpdates
2017-09-22 frontpanel dxfs
2017-10-03 Minor tweaks pre china
2017-10-31 Perplexed, PowerBus, Wobbler/Edgecutter/Tuesday updates, FinalEffect
2017-11-09 PnP files
2017-11-11 RectangularThing! (and CEM libraries)
2017-11-12 LBR fix and rectangularthing update
2017-12-05 RectangularThing R2 & KeyboardController initial commit
2017-12-05 Stabilize pitch control in RectangularTHing
2017-12-05 Folder restructure
2017-12-05 Added Production powerstrips
2018-01-03 DelayBoard
2018-01-05 RectangularThing 2 - CEM SOIC & 36HP block
2018-01-09 RectangularThing Soics
2018-01-09 filter added..
2018-01-13 RectangularThingMovings
2018-01-24 RectangularThing progress - new suboscs, separated opamps
2018-01-27 Rectangular updates & library prefix namings
2018-02-11 Tweaks & Fixes...
2018-02-13 More tiny analog tweaks..
2018-02-19 More Boards... rectthing and keyb.
2018-02-20 Board complete - elco fixes
2018-02-23 Tweaks, Powerboard, Caps in Echochamber fixed
2018-02-24 Flask tracenames for stereo debugging
2018-03-30 RectangularThing & The Rug
2018-04-05 Backlink to CADLAB.io has been added.
2018-04-07 rectthing 3, powerbus, therug, library updates
2018-04-16 Edgecutter bodge, Ardabil, Labpower, RectangularThing & Calibrator
2018-04-20 Small Utility board to drive modules that have difficulty sharing gate/cv from the busboards.
2018-06-12 Minor tweaks...
2018-07-14 RectangularThing & Fresiaboard
2018-08-14 RectangularThing production tweaks, Wobbler descriptors.
2018-08-15 Alternative frontpanel for Tuesday - designed by Endurance!
2018-08-15 previews
2018-08-17 Ardabil progress
2019-02-23 error smd mounts, library updates
2019-03-31 Small tweaks to library parts.
2019-05-31 Nein & Ardabil
2019-06-30 Ardabil update
2019-09-13 some production files
2019-09-13 production files
2019-09-17 jackdemo thingie
2019-09-20 Opl update
2019-10-21 Modules update
2019-10-21 AllOfTheAbove
2019-10-21 9pwr - opamp - testpad
2019-10-23 Dist+ added
2019-10-23 Some fixes to keep 7.7 compat
2019-10-24 Rat added with powerjumpers
2019-10-24 Commit fix
2019-10-25 Added FF&Muff schematic (.brd not updated)
2019-10-29 VCA added
2019-10-29 Updated Values
2019-10-29 5 Stompboard & library part
2019-10-30 Demoboard en Keyboard
2019-10-31 Keyboard stuff, Stompstuff, bubbles!
2019-11-04 VCA+Crossfader+Envelope+Inputs
2019-11-04 Lots of edits!
2019-11-04 Boardstuff
2019-11-04 Design file, dxf file
2019-11-04 moving stuff... POW
2019-11-05 Consistency
2019-11-05 Updated Schematic/Fixed ICs etc
    Pak de 5nov versie voor de laatste 7x!
2019-11-05 Design dingen
2019-11-05 Board edited
2019-11-05 FrontPush, keyboard model
2019-11-05 position fixes
2019-11-05 Updated board
2019-11-05 board and sch
2019-11-05 vs stuff
2019-11-06 design tweaks
2019-11-09 keyboard design
2019-11-09 Kein beetje aan het board gezeten
2019-11-11 Teensykeyboard..
2019-11-12 Finished Board placements
2019-11-12 TeensyKeyboard
2019-11-12 Pushpush
2019-11-12 12novvers
2019-11-13 Boardedits
2019-11-14 Meer boardstate
2019-11-14 Some routing, output E fix
2019-11-14 1 more fix
2019-11-15 Lijntjes trekken
2019-11-16 design tweaks - keyboard ino file
2019-11-16 16nov = Laatste versie
2019-11-17 ROUTING KLAAR
    Eindelijk
2019-11-18 Navenant.
2019-11-20 Opinionated!
2019-11-20 overstuur
2019-11-21 Speaker order - Simplekeyboard TRS midi - Overstuur design
2019-11-25 Teensy Quantize Test
2019-11-26 updates stm/quant
2019-11-27 Some stuff..
2019-11-27 board control
2019-11-27 cvouts done
2019-11-28 meer stuff aan de plank
2019-12-02 SwitchTester
2019-12-02 Switchtest update
2019-12-03 more edits to board
2019-12-03 nieuwste board!
2019-12-03 Reordered miniled pins.. and added minikeyboard
2019-12-04 Chips neergezet
2019-12-04 Added final components?
2019-12-04 board en schema sync
2019-12-04 powertesters onderin
2019-12-04 power updated
2019-12-05 extra routing... 5v voor usb
2019-12-07 board af
2019-12-09 nieuw board stm
2019-12-10 boardupdates
2019-12-12 Added Boards as Ordered before fixes
2019-12-12 nieuwe versie OVERSTUUR
2019-12-14 92 airwires to go!
2019-12-15 beetje routing
2019-12-16 bijna klaar.jpg
2019-12-16 99.9% klaar
2019-12-16 STM32 KLAAR
2019-12-16 Unsmash labels, cam export
2019-12-16 frontpanel
2019-12-16 afdesign
2019-12-19 Minikeyb, STM32
2019-12-22 Pre-ARcomp gate update
2019-12-29 AR envelope gate
2019-12-30 arboard los
2020-01-03 ARboard shenanigans
2020-02-07 Summing mixer - envelope_out link
2020-02-17 more wrong trace cleanup
2020-02-18 Update Overstuur Board
2020-02-27 RectangularThing LEDboard v1
2020-03-02 Jac Powerboard
2020-03-03 Layer Visibility for minikeyb
2020-03-06 Some overstuur resistors
2020-03-13 CNC board
2020-03-14 CNCDriver
2020-03-16 tiny overstuur schematic fixes
2020-03-24 Westlaunch as ordered
2020-04-04 Westlaunch - esp32 clap
2020-06-15 bunch of experiments + pjb things added
2020-06-15 Tunneldiode!
2020-06-25 PJB Mainboard, OPL fixes, teensyparts, powerbackpack
2020-07-10 bunch of pjb boards - tentative mixer design..
2020-07-13 simplemixer setup... not serious yet
2020-09-17 Some new boards..
2020-10-08 Bunch of stuff again..
2020-10-21 Some rotation standardization
2020-11-10 SWD isolator -pjb board progress
2020-11-24 some code and opl lib updates
2020-12-15 isolator tweaks, lbr updates
2020-12-21 zephcomponents
2020-12-21 FishStandoffs
2021-06-21 progress in the lineup..
2021-07-01 wobbler2 progress - some space
2021-07-03 wobbler and switch progress
2021-07-05 Wobbler ordered.. picolooper?
2021-07-06 looper and stuff
2021-07-08 looper...
2021-07-10 looper orderable, wobbler adjustments, fenixcase power board
2021-07-27 some board updates..
2021-07-27 Loopercode update
2021-07-27 looper things and wobbler2drum base
2021-07-28 reset position to 0 on the next clock when pressing start.
2021-07-29 more looping and wobbling
2021-09-22 Minor Updates..
2022-02-11 Update .gitignore
    ignore update
2022-02-11 Space In Kicad
2022-02-11 c&o
    criminally ornamental
2022-02-11 Space..
2022-02-23 wobbler2 and space kicad stuff
2022-02-26 Wobbler2 routed?
2022-02-27 Wobbler2 kicad
2022-03-01 wobbler2 code & sim initial
2022-03-01 wobbler2 stuff
2022-03-01 Makelists
2022-03-01 kicad touches weird files
2022-03-01 mac/windows both work now!
2022-03-03 Wobbler2 sim
2022-03-03 Wobbler2 sim includes.
2022-03-03 libfixmath ref
2022-03-04 Wobbler2 Druminstances in simulator - pattern playback
2022-03-07 Wobbler Sim Progress
2022-03-08 Wobbler2 Drummings
2022-03-17 More drumming
2022-04-01 drumming
2022-06-04 Wobbler2 Kicad Version
2022-06-04 Lots of backlog crap
